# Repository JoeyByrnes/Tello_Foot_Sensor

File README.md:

# Tello Foot Sensor
Design Files and Firmware for an Ankle Encoder + Loadcell Amplifier Combo PCB for Tello Bipedal Robot

- STM32G4 Collects sensor data and streams over CAN-FD
- Position and velocity of the AS5147U encoder is read and streamed at 1KHz
- Two loadcells are read through two ADS1220 amplifiers and streamed at 1KHz
  - Optionally, four loadcells can be connected and streamed at ~700Hz

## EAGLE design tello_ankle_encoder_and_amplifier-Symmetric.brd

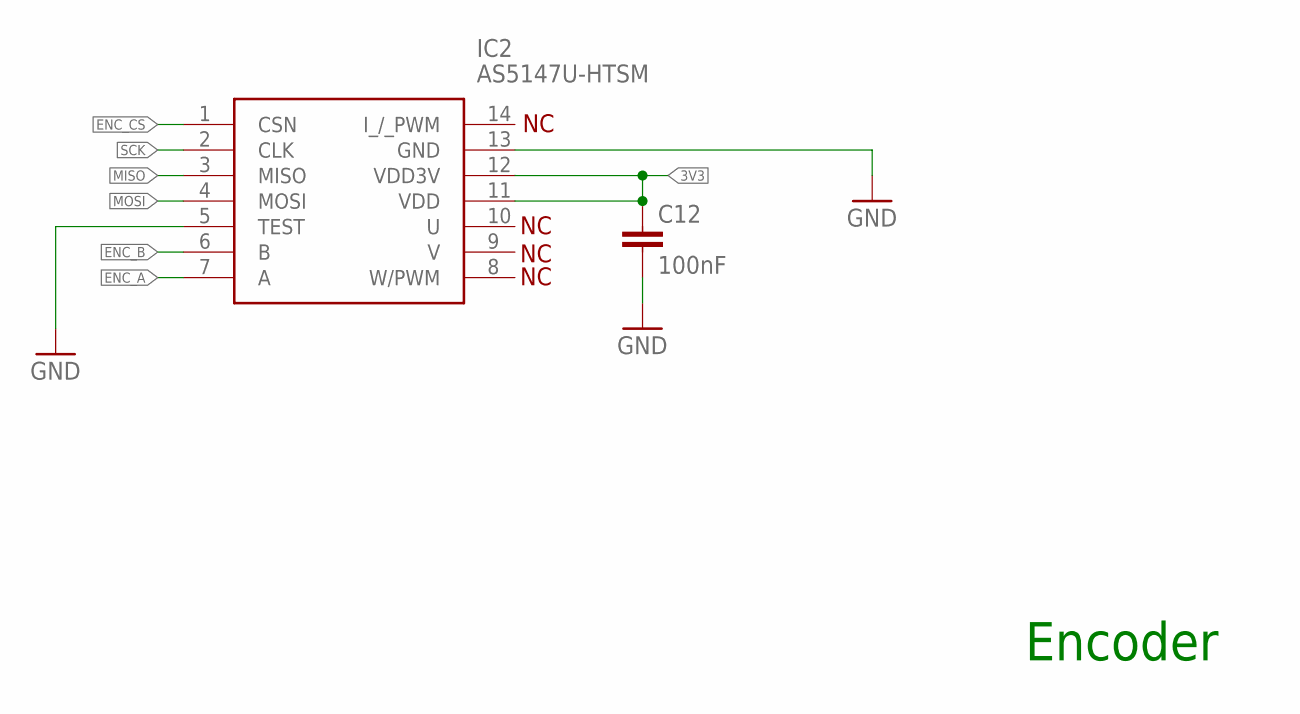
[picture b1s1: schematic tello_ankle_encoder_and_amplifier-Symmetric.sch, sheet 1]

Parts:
C12: 100nF; C0402
IC2: AS5147U-HTSM; SOP65P640X120-14N

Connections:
3V3: C12.1, IC2.11 (VDD), IC2.12 (VDD3V); also elsewhere on the board
ENC_A: IC2.7 (A); also elsewhere on the board
ENC_B: IC2.6 (B); also elsewhere on the board
ENC_CS: IC2.1 (CSN); also elsewhere on the board
GND: C12.2, IC2.5 (TEST), IC2.13 (GND); also elsewhere on the board
MISO: IC2.3 (MISO); also elsewhere on the board
MOSI: IC2.4 (MOSI); also elsewhere on the board
SCK: IC2.2 (CLK); also elsewhere on the board

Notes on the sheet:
Encoder

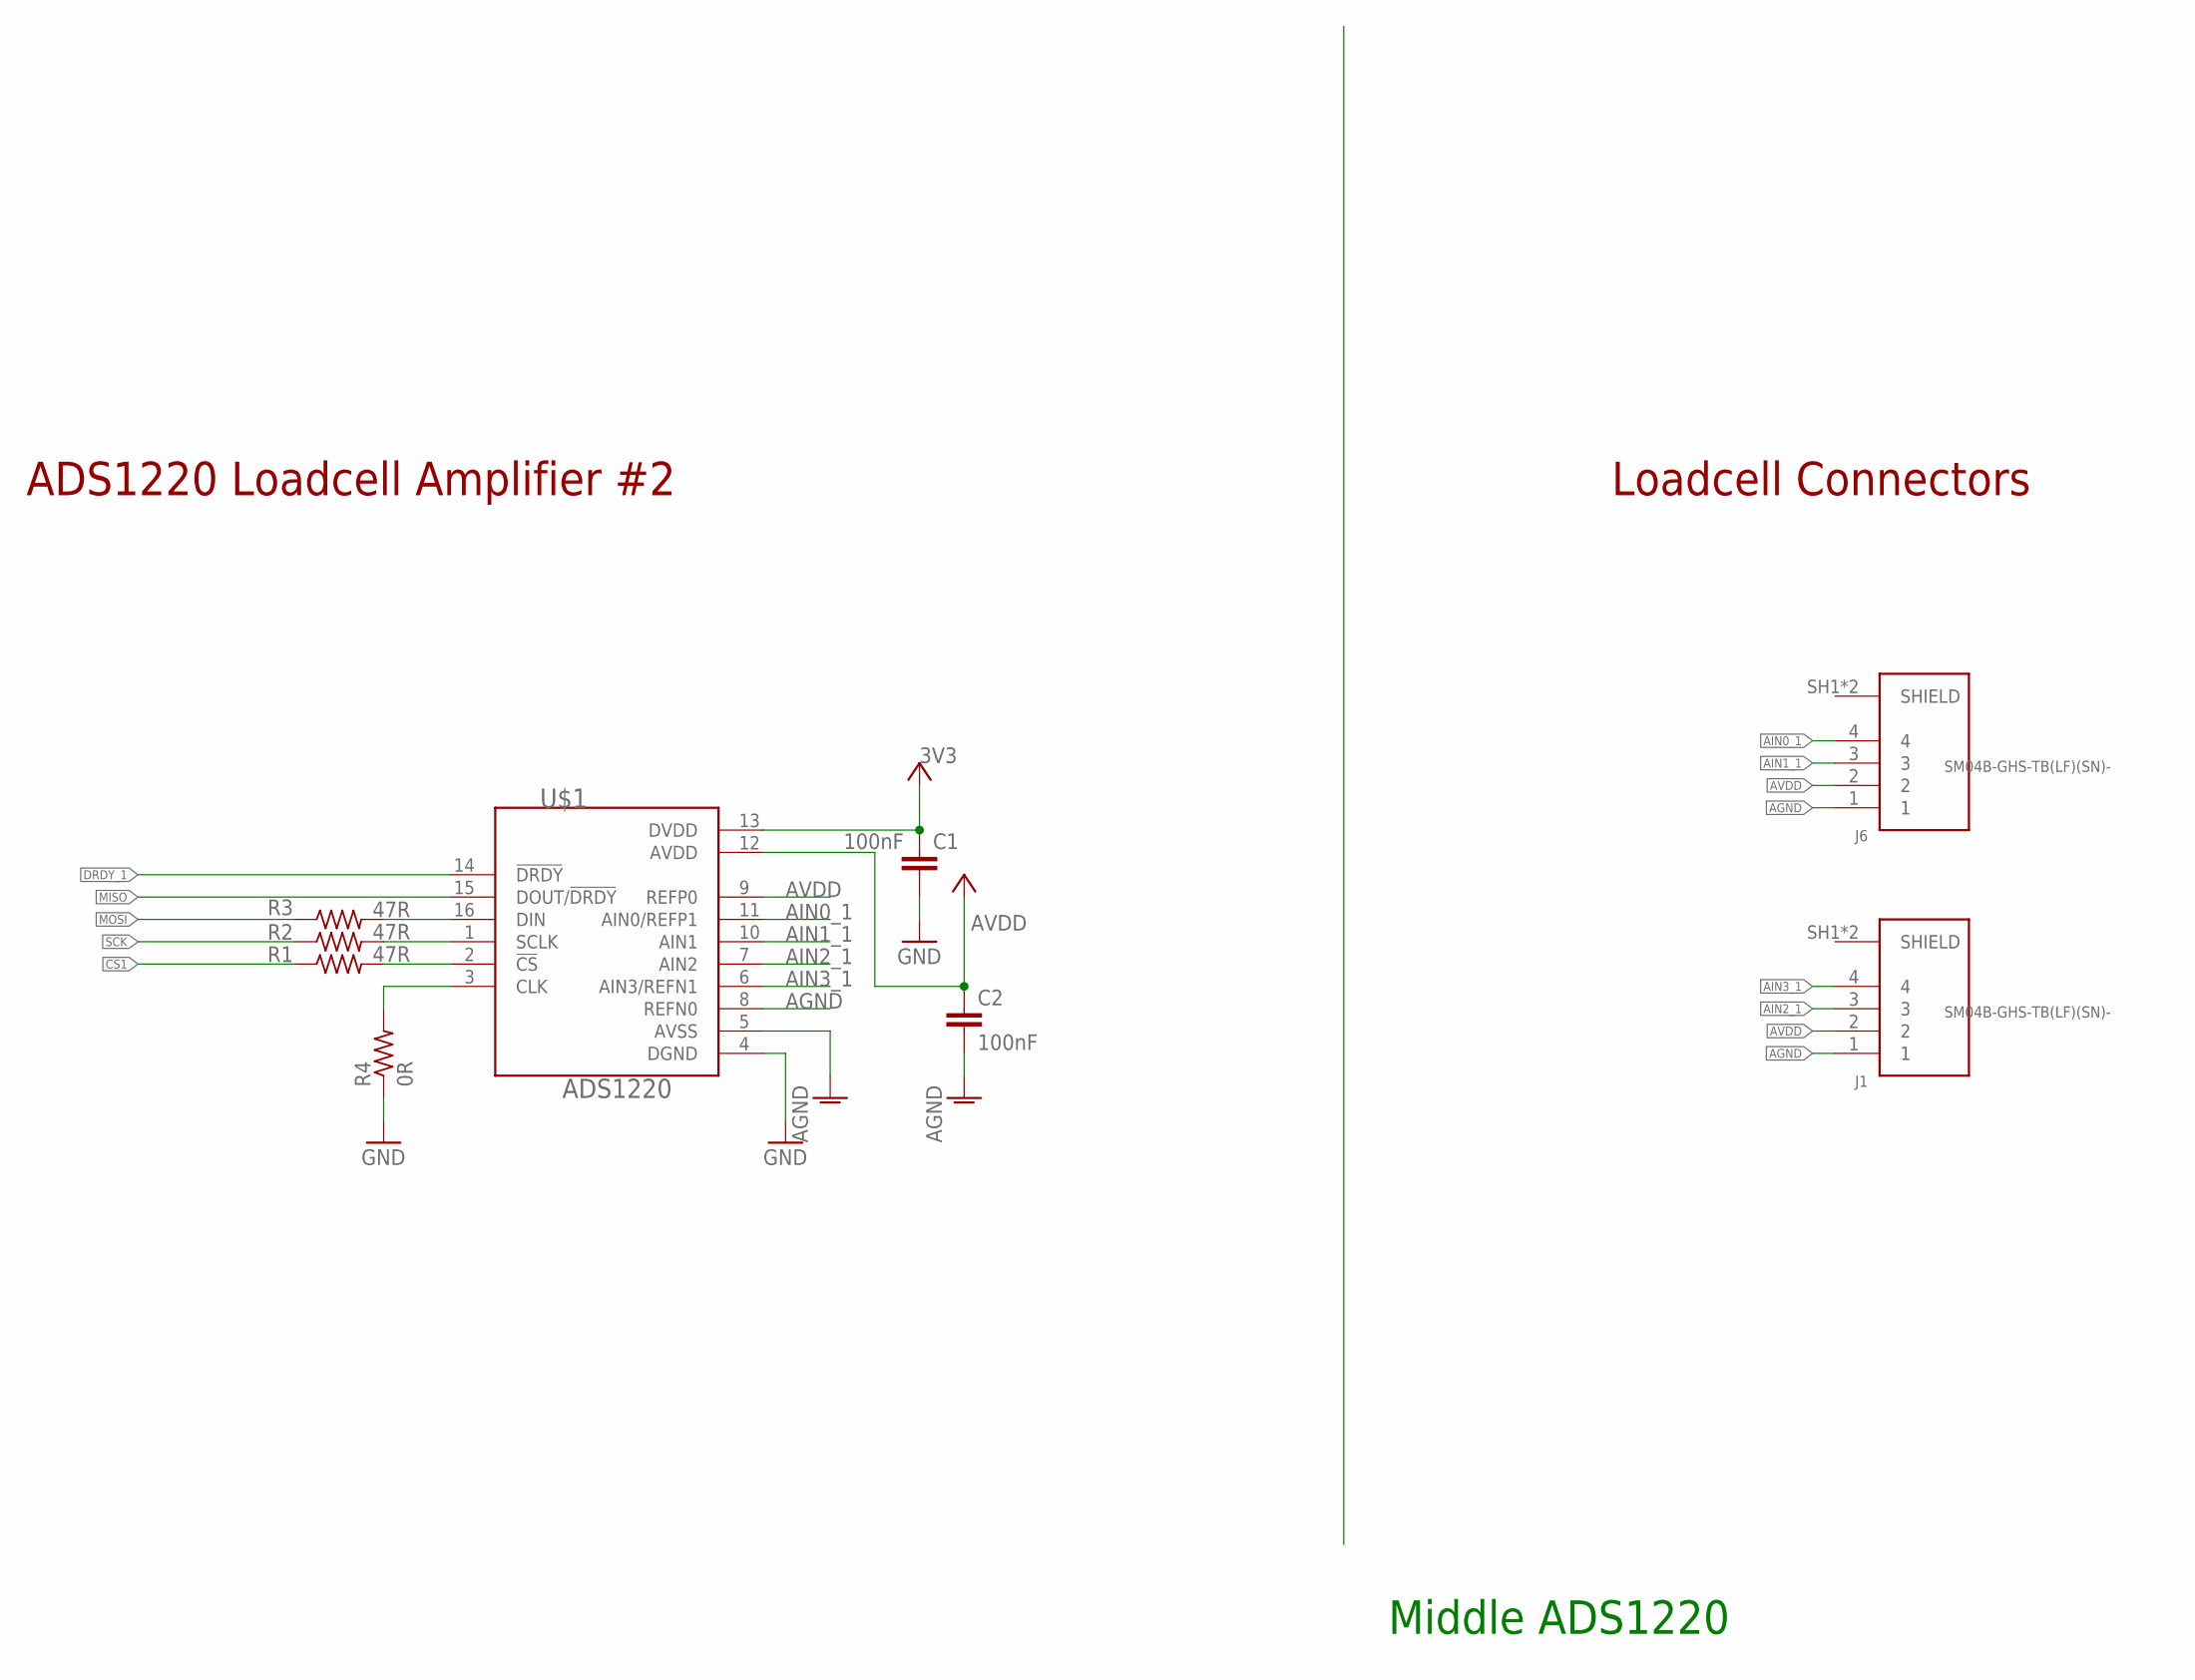
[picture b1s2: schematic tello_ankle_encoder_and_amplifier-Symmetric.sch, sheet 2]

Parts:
C1, C2: 100nF; C0402
J1, J6: SM04B-GHS-TB(LF)(SN)-; JST_SM04B-GHS-TB(LF)(SN)-
R1, R2, R3: 47R; R0402
R4: 0R; R0402
U$1: ADS1220; TSSOP-16

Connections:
3V3: C1.1, U$1.13 (DVDD); also elsewhere on the board
AGND: C2.2, J1.1, J6.1, U$1.5 (AVSS), U$1.8 (REFN0); also elsewhere on the board
AIN0_1: J6.4, U$1.11 (AIN0/REFP1)
AIN1_1: J6.3, U$1.10 (AIN1)
AIN2_1: J1.3, U$1.7 (AIN2)
AIN3_1: J1.4, U$1.6 (AIN3/REFN1)
AVDD: C2.1, J1.2, J6.2, U$1.9 (REFP0), U$1.12 (AVDD); also elsewhere on the board
CS1: R1.1; also elsewhere on the board
DRDY_1: U$1.14 (!DRDY); also elsewhere on the board
GND: C1.2, R4.1, U$1.4 (DGND); also elsewhere on the board
MISO: U$1.15 (DOUT/!DRDY); also elsewhere on the board
MOSI: R3.1; also elsewhere on the board
unnamed: R3.2, U$1.16 (DIN)
unnamed: R2.2, U$1.1 (SCLK)
unnamed: R1.2, U$1.2 (!CS)
unnamed: R4.2, U$1.3 (CLK)
SCK: R2.1; also elsewhere on the board
SHIELD: J1.SH1 (SHIELD), J1.SH2 (SHIELD), J6.SH1 (SHIELD), J6.SH2 (SHIELD); also elsewhere on the board

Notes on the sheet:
Middle ADS1220
ADS1220 Loadcell Amplifier #2
Loadcell Connectors

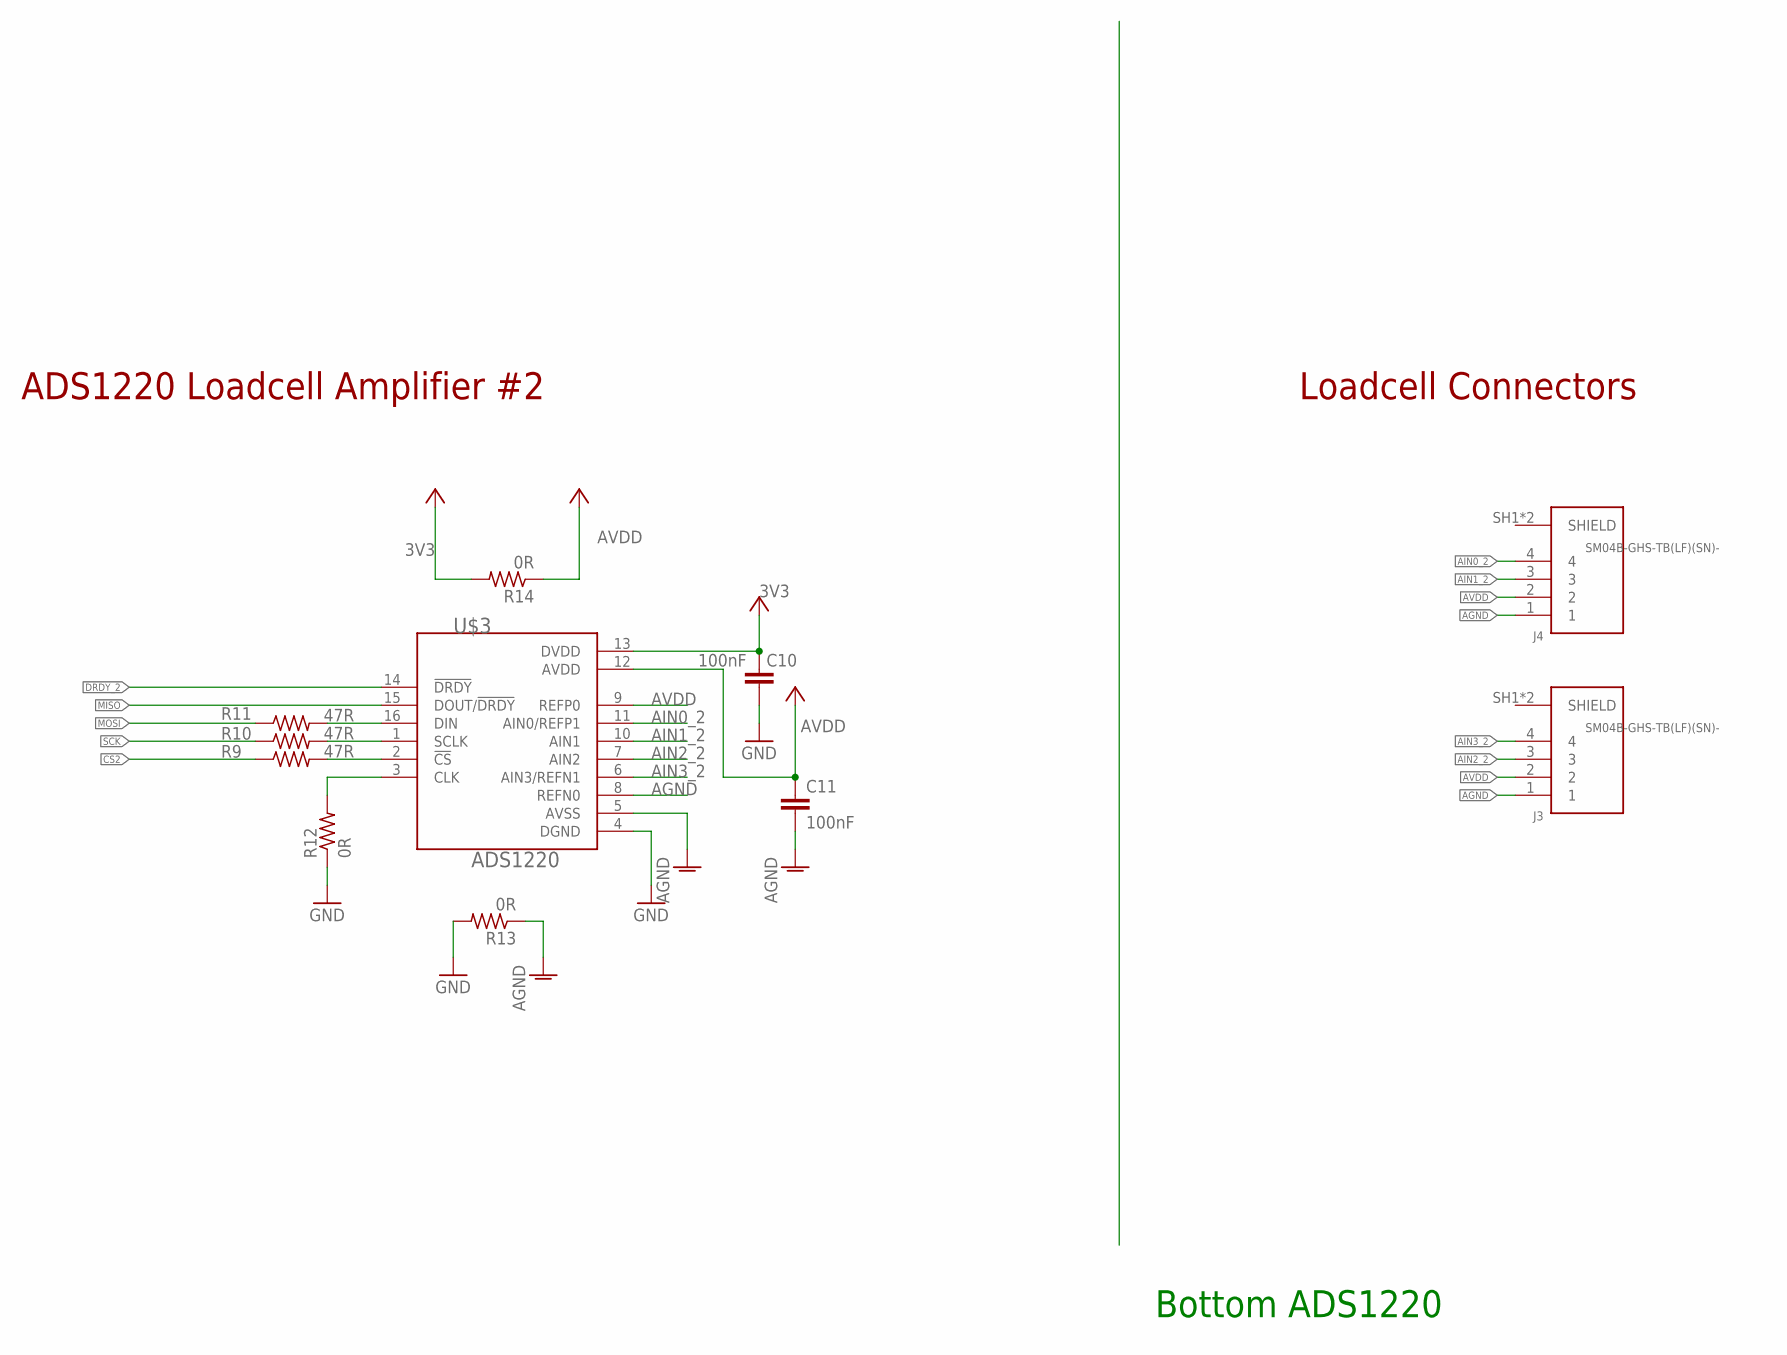
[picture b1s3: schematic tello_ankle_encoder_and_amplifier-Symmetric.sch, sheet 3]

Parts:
C10, C11: 100nF; C0402
J3, J4: SM04B-GHS-TB(LF)(SN)-; JST_SM04B-GHS-TB(LF)(SN)-
R9, R10, R11: 47R; R0402
R12, R13, R14: 0R; R0402
U$3: ADS1220; TSSOP-16

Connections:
3V3: C10.1, R14.2, U$3.13 (DVDD); also elsewhere on the board
AGND: C11.2, J3.1, J4.1, R13.1, U$3.5 (AVSS), U$3.8 (REFN0); also elsewhere on the board
AIN0_2: J4.4, U$3.11 (AIN0/REFP1)
AIN1_2: J4.3, U$3.10 (AIN1)
AIN2_2: J3.3, U$3.7 (AIN2)
AIN3_2: J3.4, U$3.6 (AIN3/REFN1)
AVDD: C11.1, J3.2, J4.2, R14.1, U$3.9 (REFP0), U$3.12 (AVDD); also elsewhere on the board
CS2: R9.1; also elsewhere on the board
DRDY_2: U$3.14 (!DRDY); also elsewhere on the board
GND: C10.2, R12.1, R13.2, U$3.4 (DGND); also elsewhere on the board
MISO: U$3.15 (DOUT/!DRDY); also elsewhere on the board
MOSI: R11.1; also elsewhere on the board
unnamed: R11.2, U$3.16 (DIN)
unnamed: R10.2, U$3.1 (SCLK)
unnamed: R9.2, U$3.2 (!CS)
unnamed: R12.2, U$3.3 (CLK)
SCK: R10.1; also elsewhere on the board
SHIELD: J3.SH1 (SHIELD), J3.SH2 (SHIELD), J4.SH1 (SHIELD), J4.SH2 (SHIELD); also elsewhere on the board

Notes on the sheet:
Bottom ADS1220
ADS1220 Loadcell Amplifier #2
Loadcell Connectors

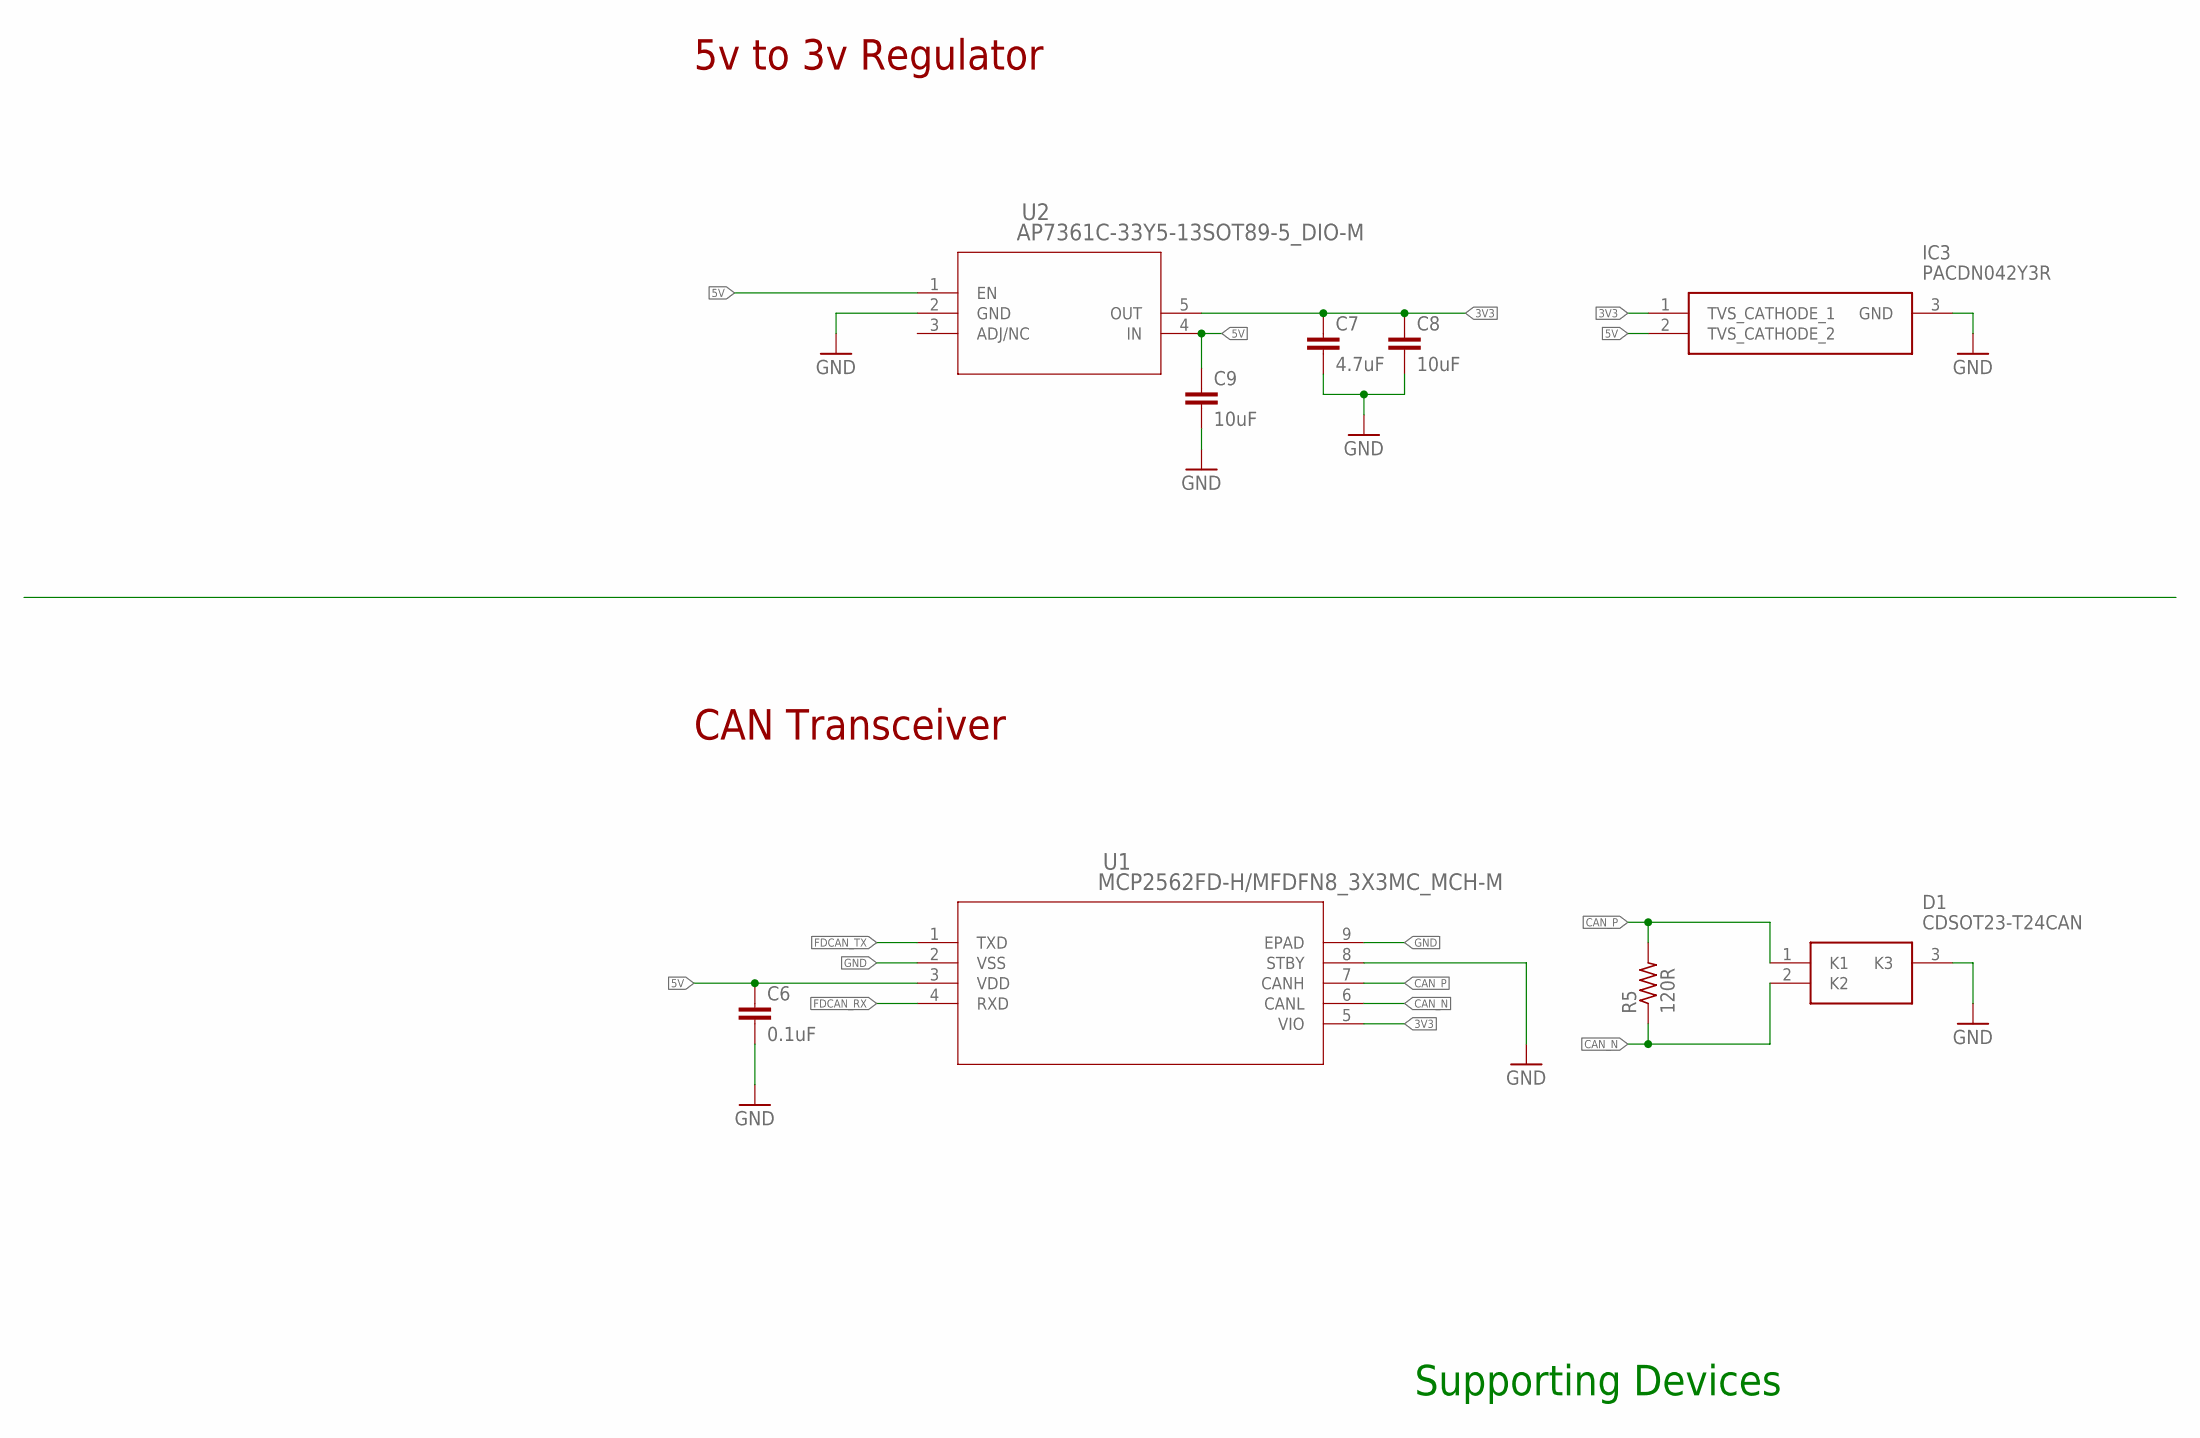
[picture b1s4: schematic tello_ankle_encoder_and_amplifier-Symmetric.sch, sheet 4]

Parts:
C6: 0.1uF; C0603
C7: 4.7uF; C0603
C8, C9: 10uF; C0603
D1: CDSOT23-T24CAN; SOT95P230X117-3N
IC3: PACDN042Y3R; SOT96P237X111-3N
R5: 120R; R0402
U1: MCP2562FD-H/MFDFN8_3X3MC_MCH-M; DFN8_3X3MC_MCH-M
U2: AP7361C-33Y5-13SOT89-5_DIO-M; SOT89-5_DIO-M

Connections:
3V3: C7.1, C8.1, IC3.1 (TVS_CATHODE_1), U1.5 (VIO), U2.5 (OUT); also elsewhere on the board
5V: C6.1, C9.1, IC3.2 (TVS_CATHODE_2), U1.3 (VDD), U2.1 (EN), U2.4 (IN); also elsewhere on the board
CAN_N: D1.2 (K2), R5.1, U1.6 (CANL); also elsewhere on the board
CAN_P: D1.1 (K1), R5.2, U1.7 (CANH); also elsewhere on the board
FDCAN_RX: U1.4 (RXD); also elsewhere on the board
FDCAN_TX: U1.1 (TXD); also elsewhere on the board
GND: C6.2, C7.2, C8.2, C9.2, D1.3 (K3), IC3.3 (GND), U1.2 (VSS), U1.8 (STBY), U1.9 (EPAD), U2.2 (GND); also elsewhere on the board

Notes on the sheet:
5v to 3v Regulator
CAN Transceiver
Supporting Devices

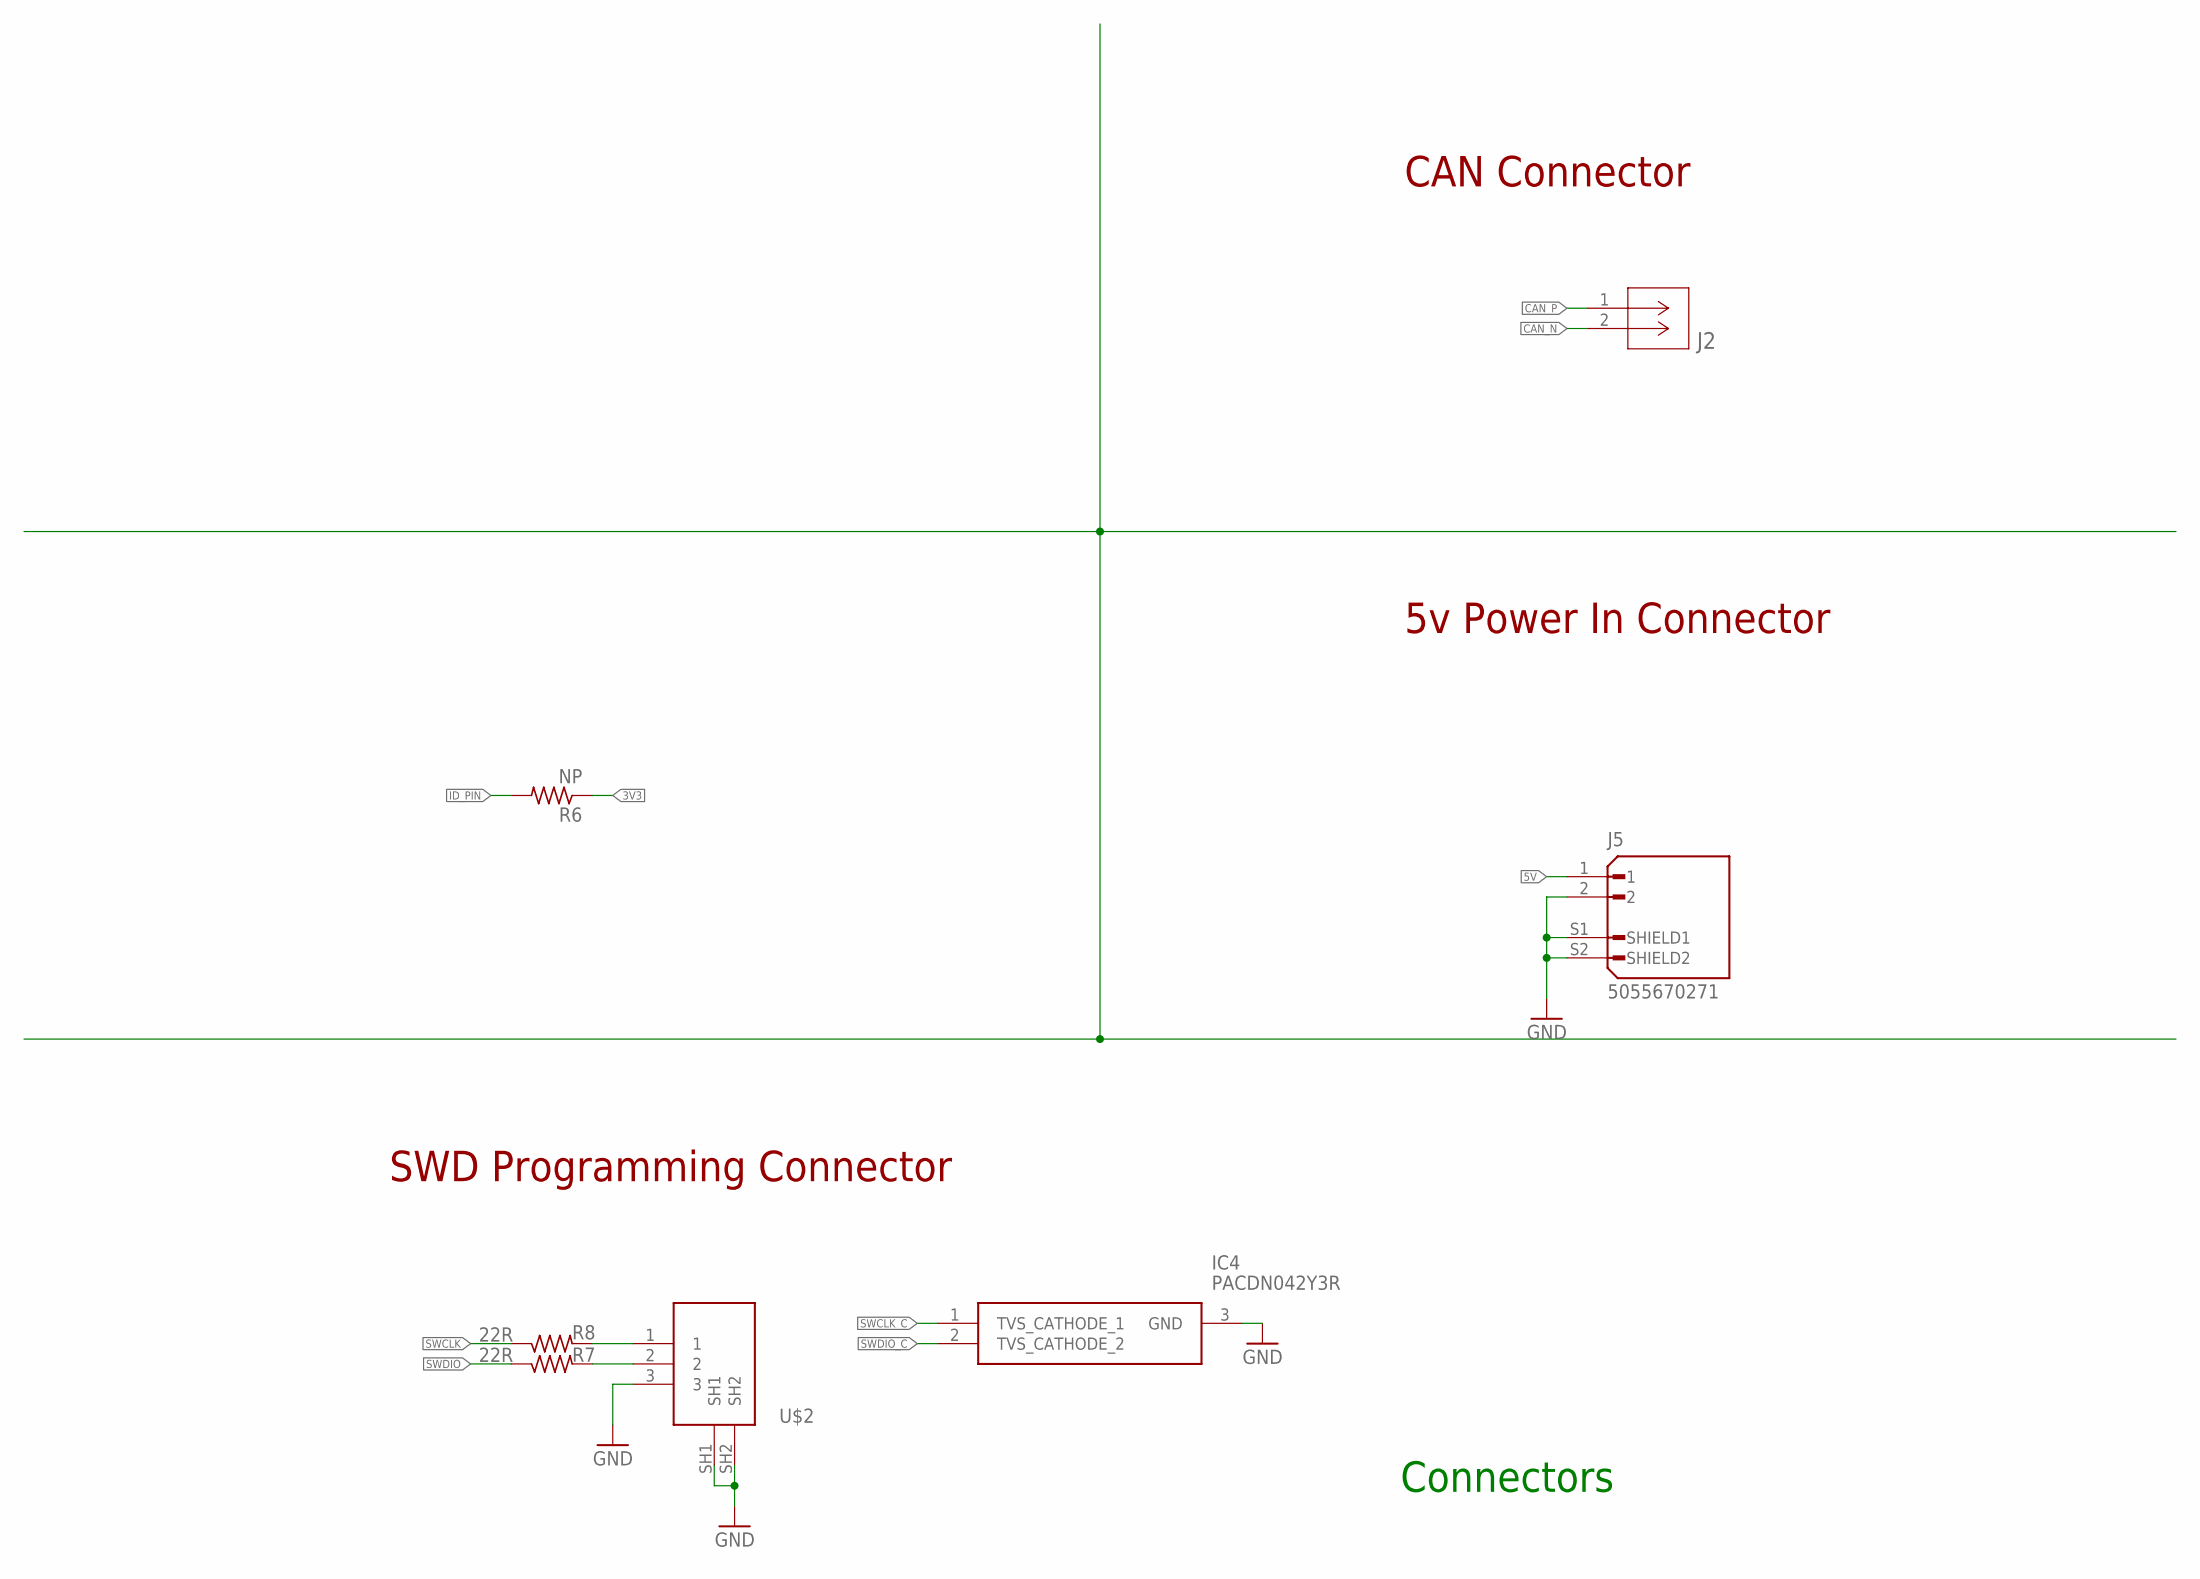
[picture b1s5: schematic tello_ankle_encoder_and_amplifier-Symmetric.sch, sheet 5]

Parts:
IC4: PACDN042Y3R; SOT96P237X111-3N
J2: SM02BGHSTBLFSN; CONN_SM02BGHSTB_JST
J5: 5055670271; MOLEX_5055670271
R6: NP; R0402
R7, R8: 22R; R0402
U$2: 125SH-G-03-TR-SMT

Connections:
3V3: R6.1; also elsewhere on the board
5V: J5.1; also elsewhere on the board
CAN_N: J2.2; also elsewhere on the board
CAN_P: J2.1; also elsewhere on the board
GND: IC4.3 (GND), J5.2, J5.S1 (SHIELD1), J5.S2 (SHIELD2), U$2.3, U$2.SH1, U$2.SH2; also elsewhere on the board
ID_PIN: R6.2; also elsewhere on the board
SWCLK: R8.1; also elsewhere on the board
SWCLK_C: IC4.1 (TVS_CATHODE_1), R8.2, U$2.1
SWDIO: R7.1; also elsewhere on the board
SWDIO_C: IC4.2 (TVS_CATHODE_2), R7.2, U$2.2

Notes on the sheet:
U$2
CAN Connector
5v Power In Connector
SWD Programming Connector
Connectors

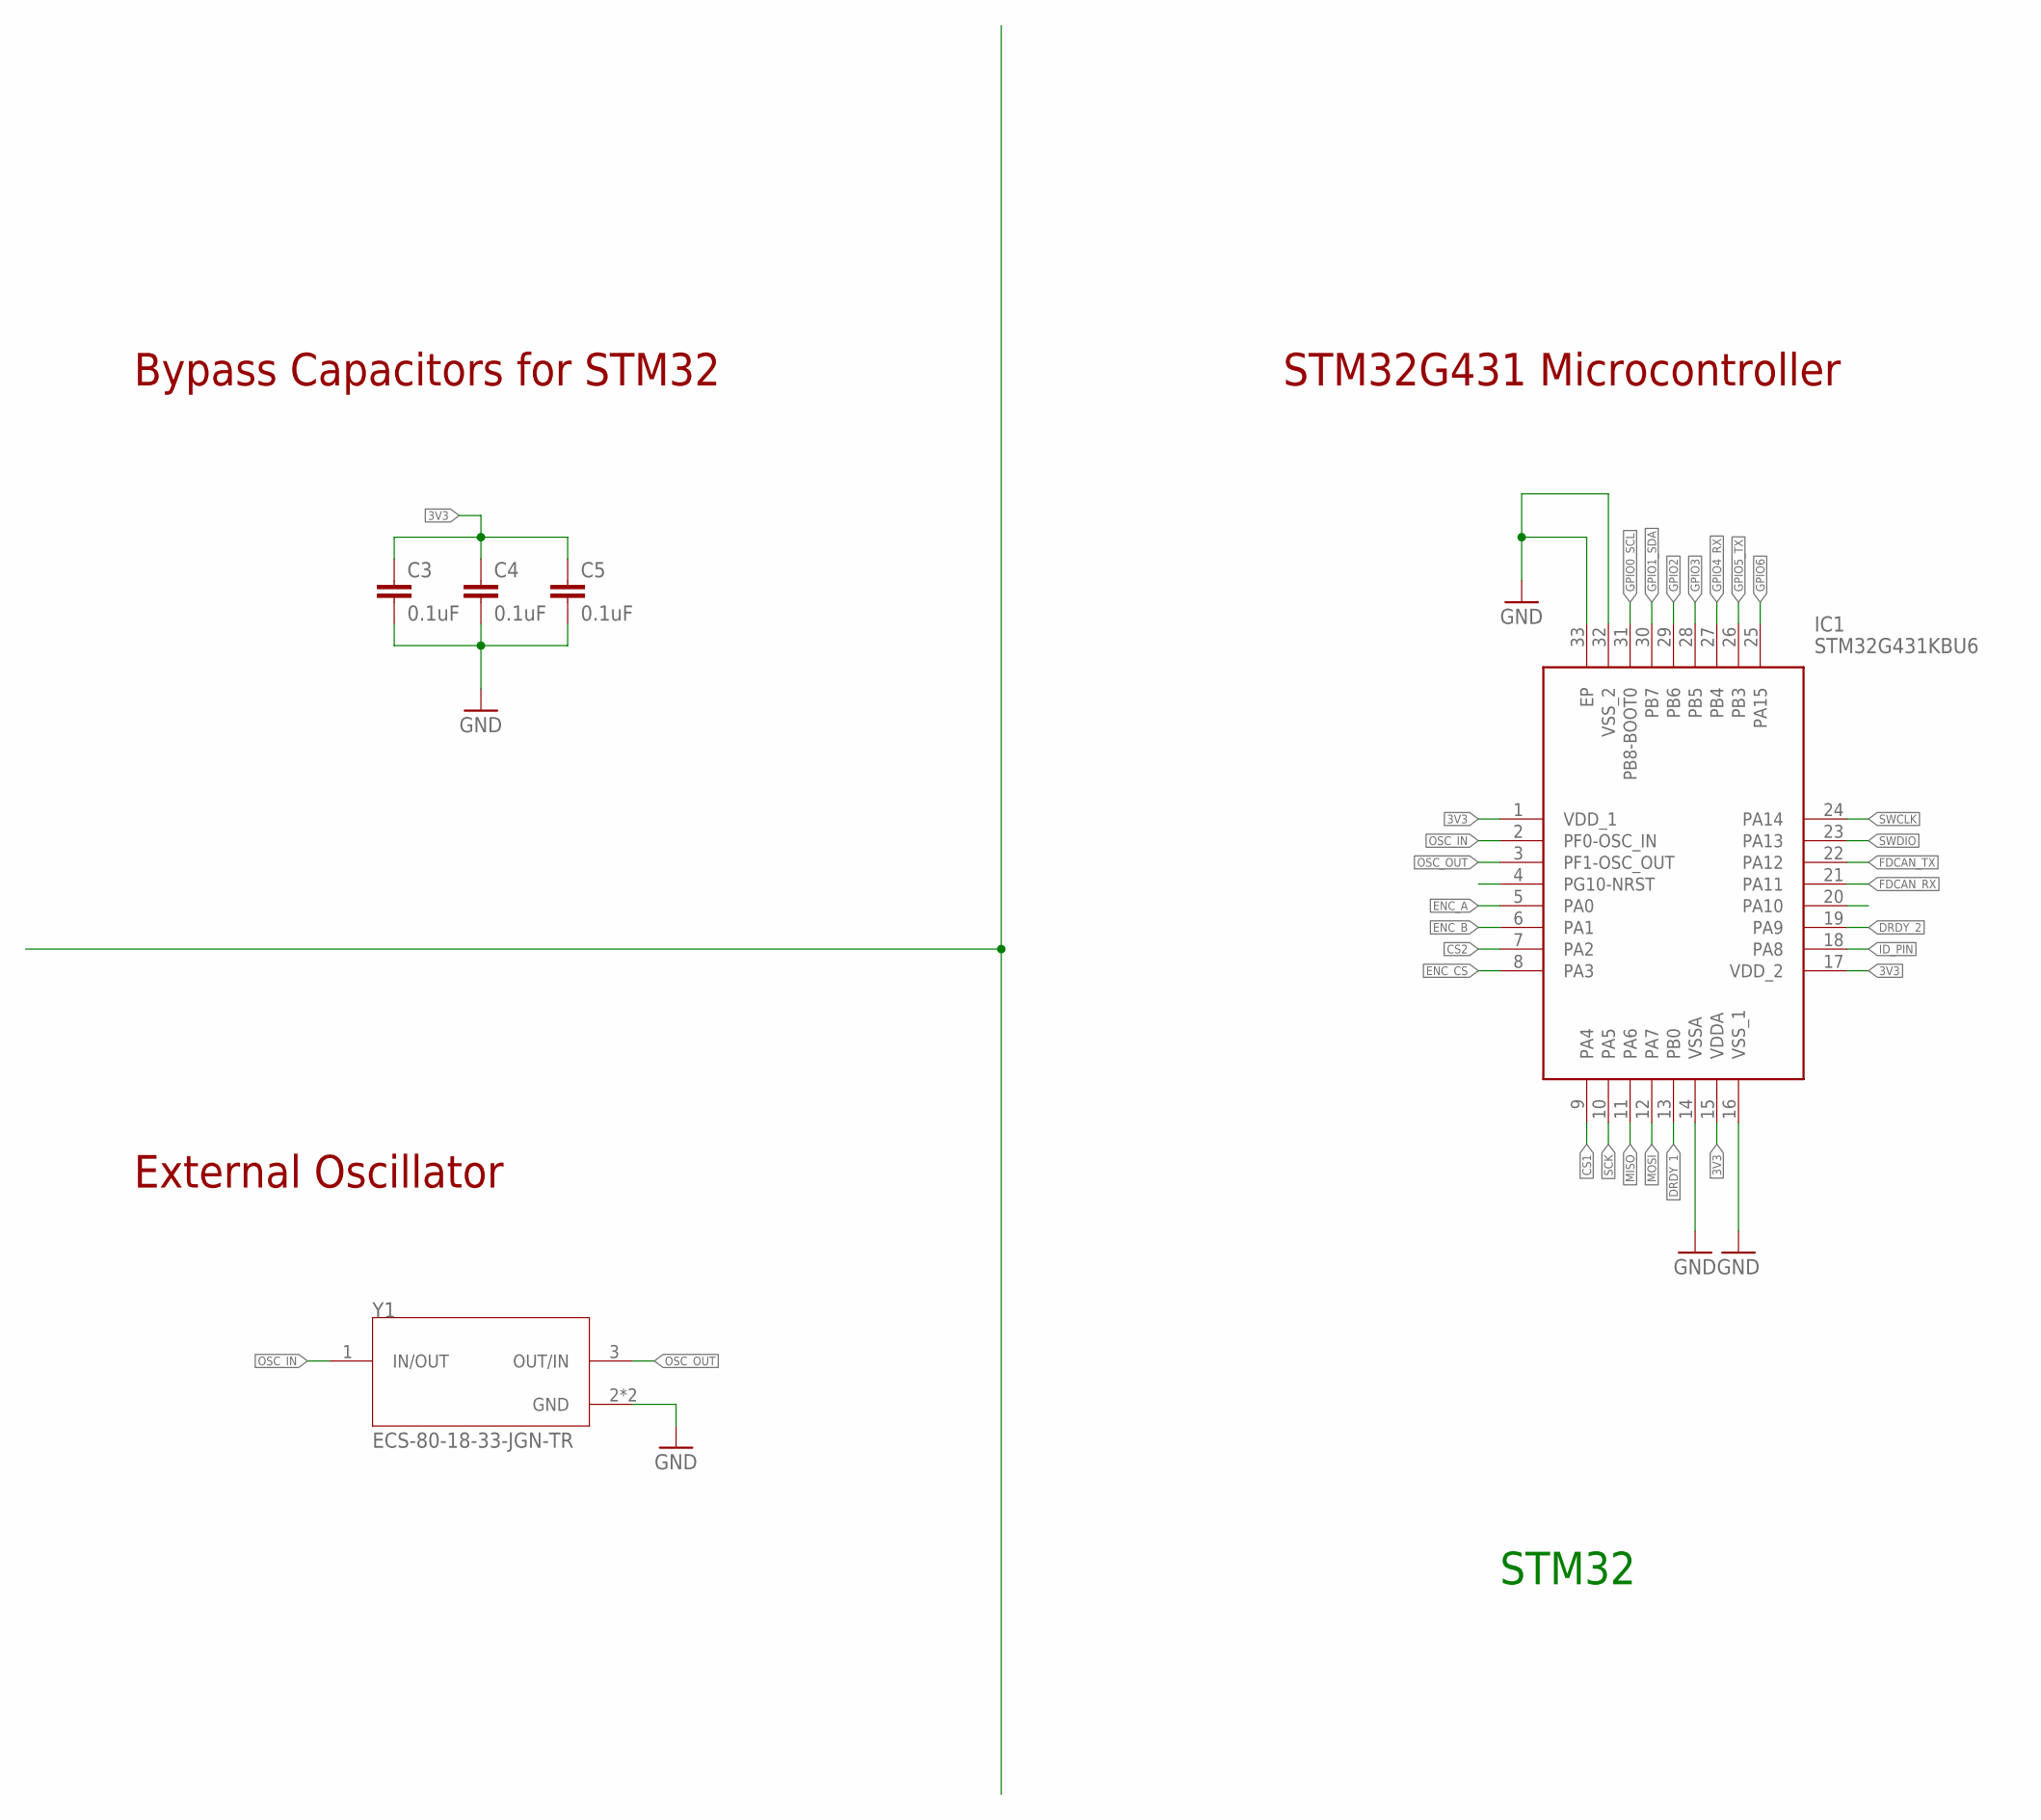
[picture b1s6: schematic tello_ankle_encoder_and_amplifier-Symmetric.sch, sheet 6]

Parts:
C3, C4, C5: 0.1uF; C0402
IC1: STM32G431KBU6; QFN50P500X500X60-33N
Y1: ECS-80-18-33-JGN-TR; XTAL_ECS-240-8-33-AGN-TR

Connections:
3V3: C3.1, C4.1, C5.1, IC1.1 (VDD_1), IC1.15 (VDDA), IC1.17 (VDD_2); also elsewhere on the board
CS1: IC1.9 (PA4); also elsewhere on the board
CS2: IC1.7 (PA2); also elsewhere on the board
DRDY_1: IC1.13 (PB0); also elsewhere on the board
DRDY_2: IC1.19 (PA9); also elsewhere on the board
ENC_A: IC1.5 (PA0); also elsewhere on the board
ENC_B: IC1.6 (PA1); also elsewhere on the board
ENC_CS: IC1.8 (PA3); also elsewhere on the board
FDCAN_RX: IC1.21 (PA11); also elsewhere on the board
FDCAN_TX: IC1.22 (PA12); also elsewhere on the board
GND: C3.2, C4.2, C5.2, IC1.14 (VSSA), IC1.16 (VSS_1), IC1.32 (VSS_2), IC1.33 (EP), Y1.2 (GND), Y1.4 (GND); also elsewhere on the board
GPIO0_SCL: IC1.31 (PB8-BOOT0)
GPIO1_SDA: IC1.30 (PB7)
GPIO2: IC1.29 (PB6)
GPIO3: IC1.28 (PB5)
GPIO4_RX: IC1.27 (PB4)
GPIO5_TX: IC1.26 (PB3)
GPIO6: IC1.25 (PA15)
ID_PIN: IC1.18 (PA8); also elsewhere on the board
MISO: IC1.11 (PA6); also elsewhere on the board
MOSI: IC1.12 (PA7); also elsewhere on the board
OSC_IN: IC1.2 (PF0-OSC_IN), Y1.1 (IN/OUT)
OSC_OUT: IC1.3 (PF1-OSC_OUT), Y1.3 (OUT/IN)
SCK: IC1.10 (PA5); also elsewhere on the board
SWCLK: IC1.24 (PA14); also elsewhere on the board
SWDIO: IC1.23 (PA13); also elsewhere on the board

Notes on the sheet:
Bypass Capacitors for STM32
External Oscillator
STM32G431 Microcontroller
STM32

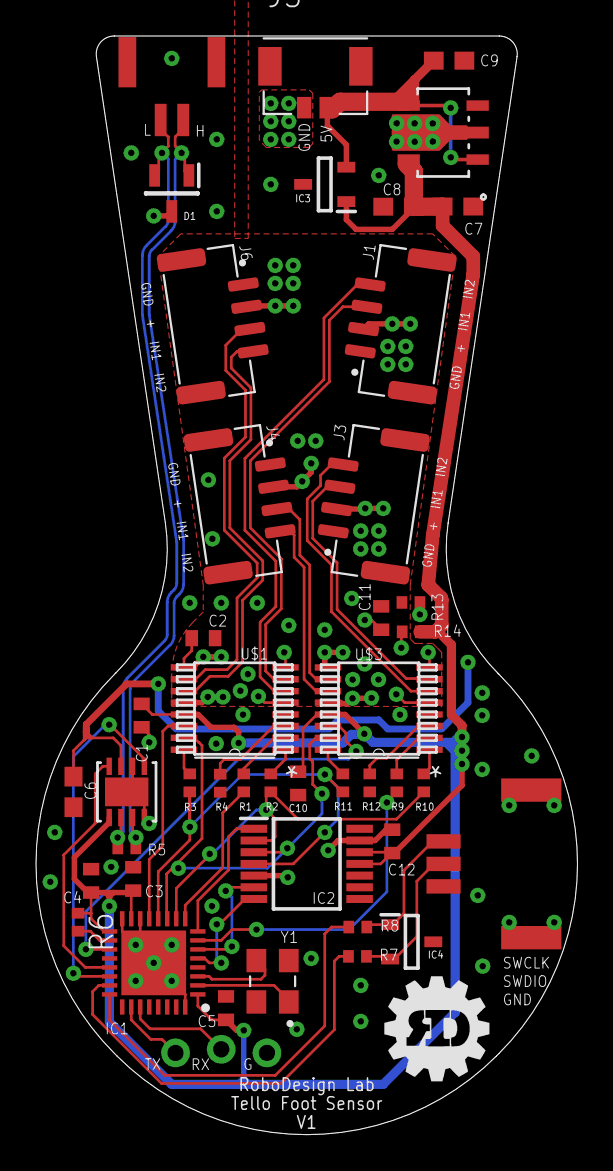
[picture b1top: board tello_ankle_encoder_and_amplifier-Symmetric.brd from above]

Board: 4 copper layers, 30.1 x 61.0 mm, 43 parts (0 on the bottom side), 43 nets.

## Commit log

2023-08-16 board reviewed once
2023-10-02 added manufacturing files
2023-10-02 updated manufacturing files
2023-10-04 added design files and firmware

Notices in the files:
parts and their libraries:
COPYRIGHT: Copyright (C) 2023 Ultra Librarian. All rights reserved.
COPYRIGHT: Copyright (C) 2022 Ultra Librarian. All rights reserved.
